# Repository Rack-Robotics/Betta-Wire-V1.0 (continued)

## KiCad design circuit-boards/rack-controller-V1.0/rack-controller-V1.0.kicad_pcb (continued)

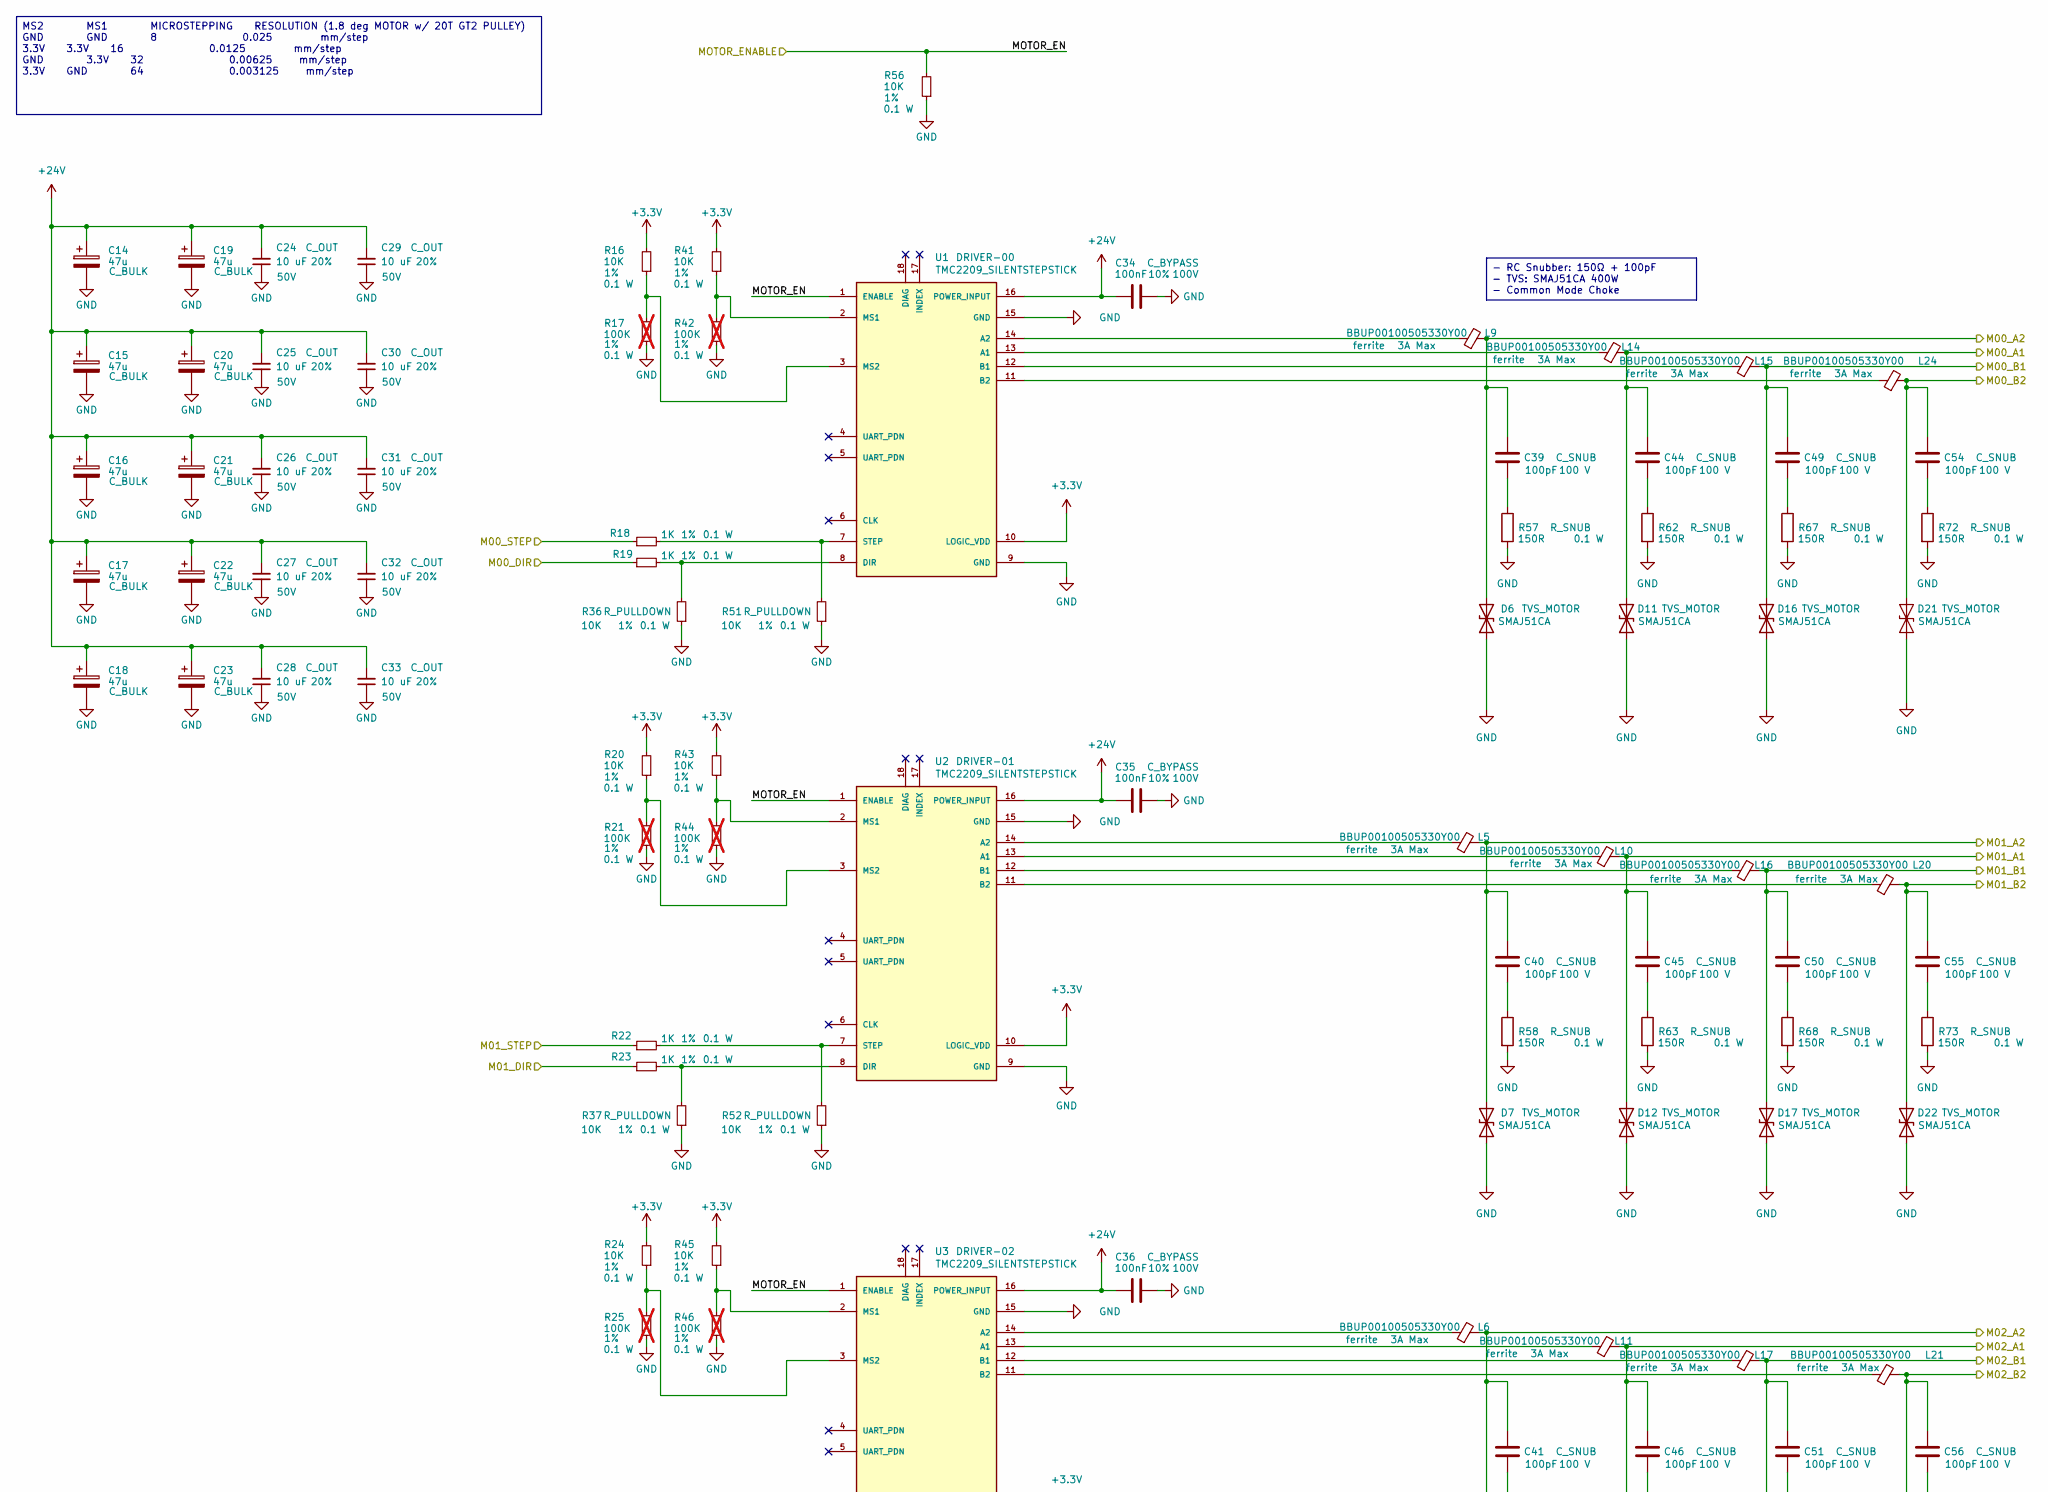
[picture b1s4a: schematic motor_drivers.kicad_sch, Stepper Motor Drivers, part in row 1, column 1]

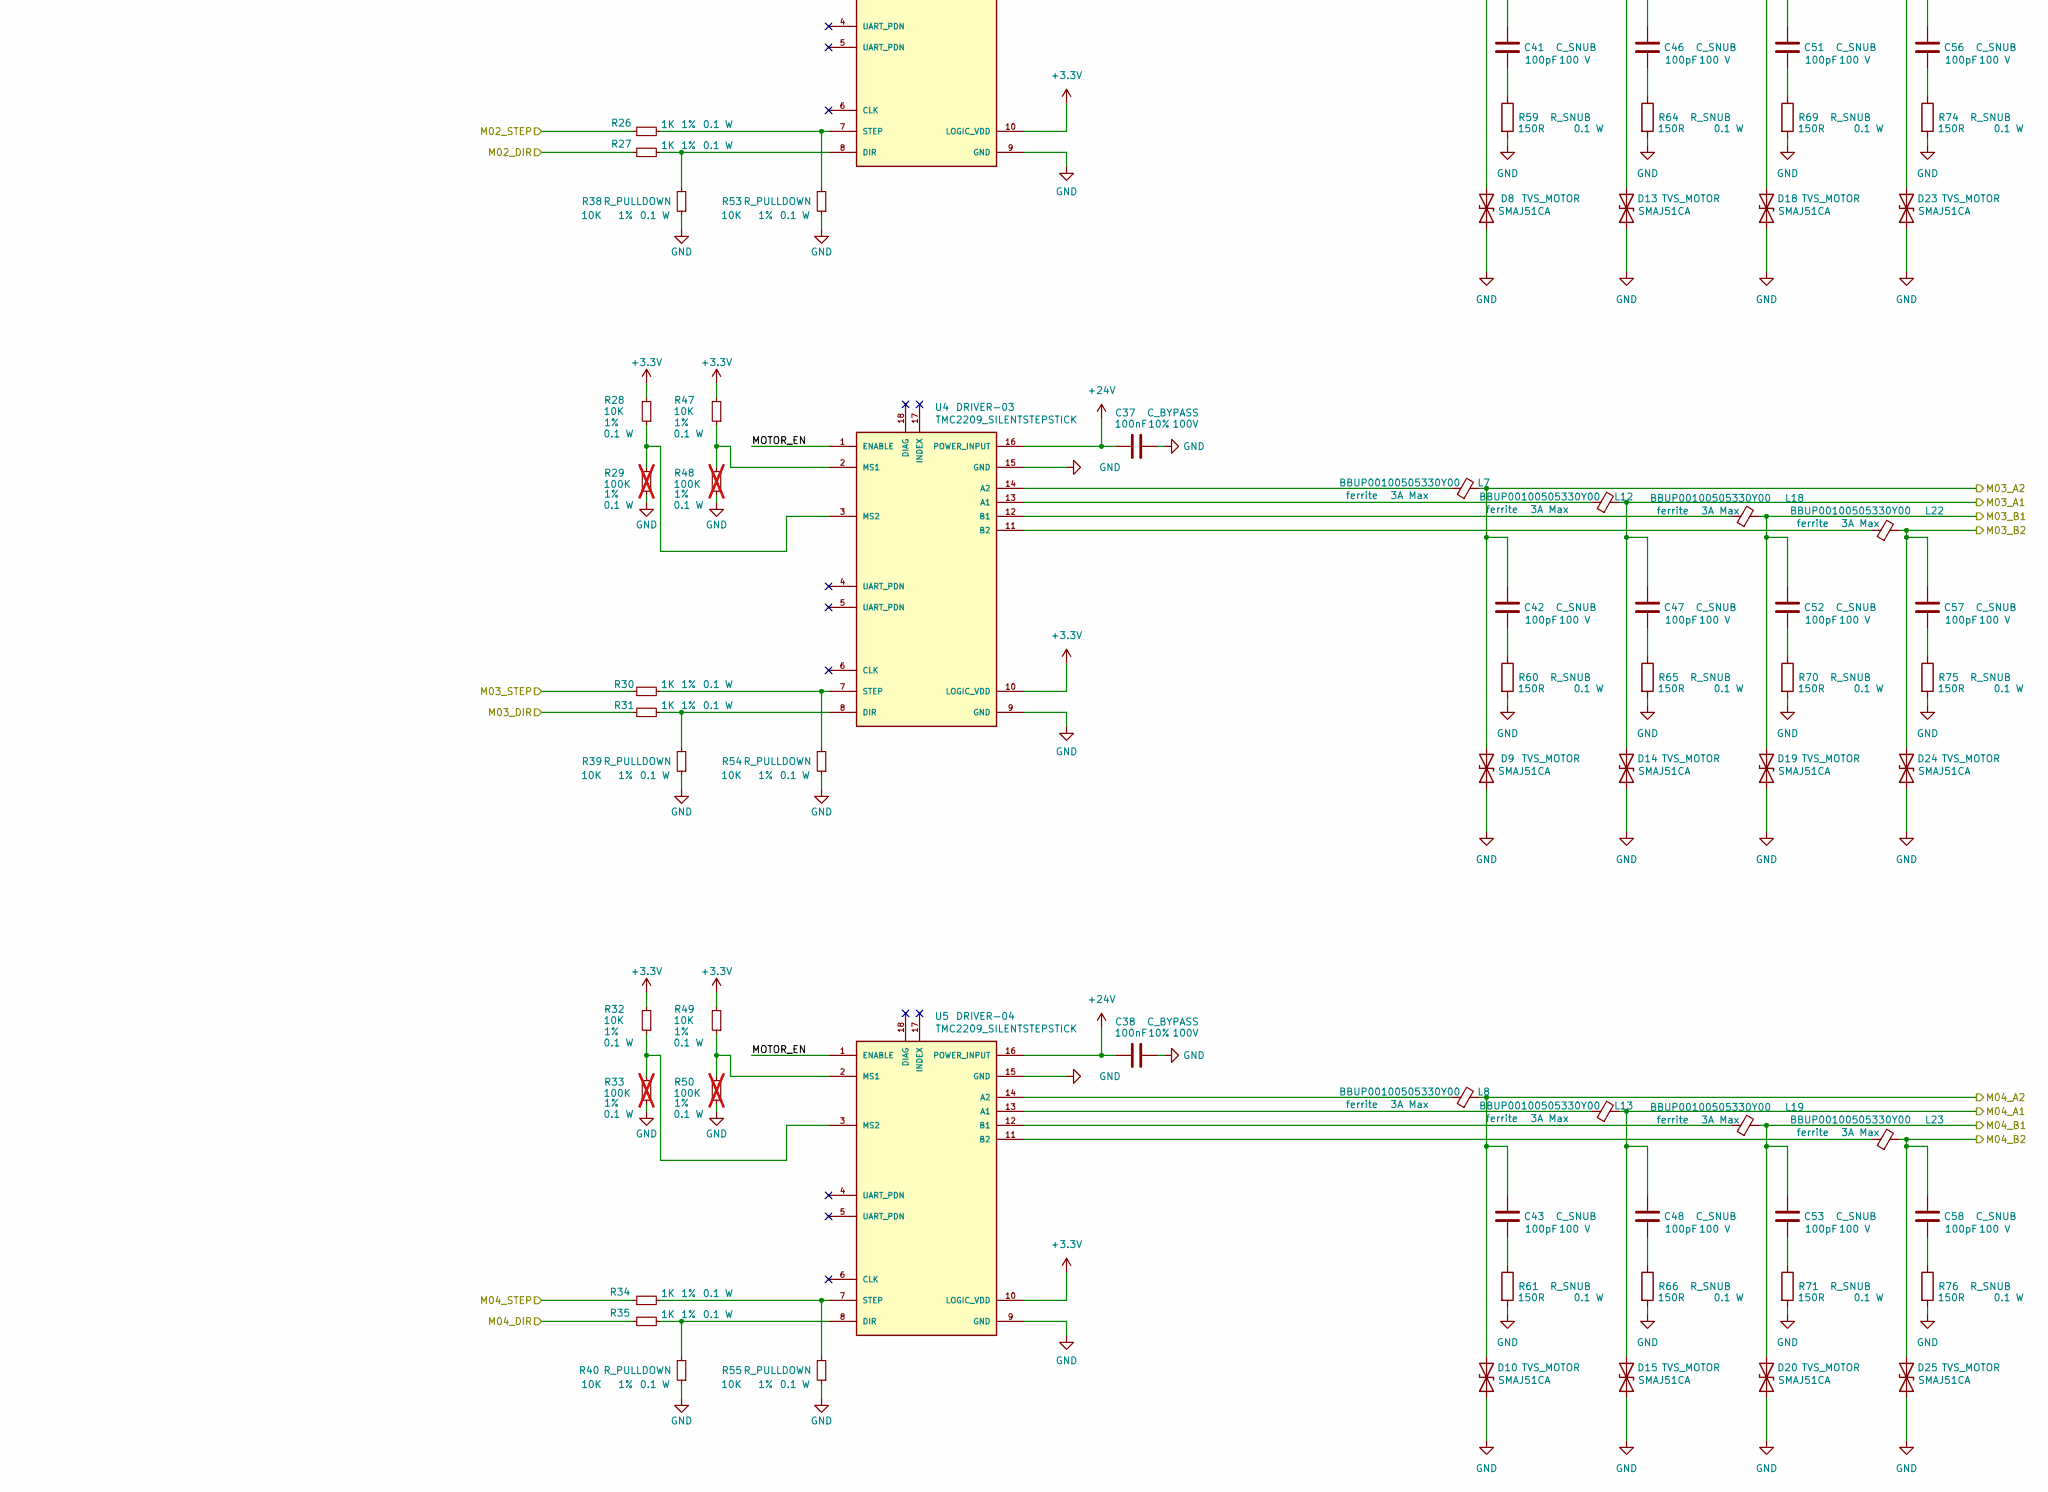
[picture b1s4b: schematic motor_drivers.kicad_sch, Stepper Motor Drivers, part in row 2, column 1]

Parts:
C14, C15, C16, C17, C18, C19, C20, C21, C22, C23: 47u; CP_Elec_6.3x5.9; Manufacturer# 35SVPK47M; LCSC Part # C264034
C24, C25, C26, C27, C28, C29, C30, C31, C32, C33: 10 uF; C_1206_3216Metric; Tolerance 20%; Max Voltage 50V; Manufacturer# CL31A106MBHNNNE; LCSC Part # C96600
C34, C35, C36, C37, C38: 100nF; C_0603_1608Metric; Voltage 100V; Tolerance 10%; Manufacturer# CC0603KRX7R0BB104; LCSC Part # C113803
C39, C40, C41, C42, C43, C44, C45, C46, C47, C48, C49, C50, C51, C52, C53, C54, C55, C56, C57, C58: 100pF; C_0402_1005Metric; Voltage 100 V; Manufacturer# CC0402JRNPO0BN101; LCSC Part # C576700
D6, D7, D8, D9, D10, D11, D12, D13, D14, D15, D16, D17, D18, D19, D20, D21, D22, D23, D24, D25: SMAJ51CA; D_SMA; Manufacturer# SMAJ60CA-13-F; LCSC Part # C135003
L5, L6, L7, L8, L9, L10, L11, L12, L13, L14, L15, L16, L17, L18, L19, L20, L21, L22, L23, L24: BBUP00100505330Y00; L_0402_1005Metric; Manufacturer# BLM15AX100SN1D; LCSC Part # C668299
R16, R20, R24, R28, R32, R36, R37, R38, R39, R40, R41, R43, R45, R47, R49, R51, R52, R53, R54, R55, R56: 10K; R_0603_1608Metric; Tolerance 1%; Manufacturer# RC0603BR-0710KL; LCSC Part # C98220
R17, R21, R25, R29, R33, R42, R44, R46, R48, R50: 100K; R_0603_1608Metric; Tolerance 1%; Manufacturer# RT0603FRE07100KL; LCSC Part # C728638; not fitted
R18, R19, R22, R23, R26, R27, R30, R31, R34, R35: 1K; R_0603_1608Metric; Tolerance 1%; Manufacturer# RC0603FR-071KL; LCSC Part # C22548
R57, R58, R59, R60, R61, R62, R63, R64, R65, R66, R67, R68, R69, R70, R71, R72, R73, R74, R75, R76: 150R; R_0603_1608Metric; Tolerance 1%; Manufacturer# RC0603FR-07150RL; LCSC Part # C114608
U1, U2, U3, U4, U5: TMC2209_SILENTSTEPSTICK; BTT_TMC2209_V1.3; Manufacturer# TMC2209_V1.3; LCSC Part # NULL

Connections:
+3.3V: R16.2, R20.2, R24.2, R28.2, R32.2, R41.2, R43.2, R45.2, R47.2, R49.2, U1.10 (LOGIC_VDD), U2.10 (LOGIC_VDD), U3.10 (LOGIC_VDD), U4.10 (LOGIC_VDD), U5.10 (LOGIC_VDD); also elsewhere on the board
+24V: C14.1, C15.1, C16.1, C17.1, C18.1, C19.1, C20.1, C21.1, C22.1, C23.1, C24.2, C25.2, C26.2, C27.2, C28.2, C29.2, C30.2, C31.2, C32.2, C33.2, C34.2, C35.2, C36.2, C37.2, C38.2, U1.16 (POWER_INPUT), U2.16 (POWER_INPUT), U3.16 (POWER_INPUT), U4.16 (POWER_INPUT), U5.16 (POWER_INPUT); also elsewhere on the board
/GPIO_05: R18.1; also elsewhere on the board
/GPIO_06: R56.2, U1.1 (ENABLE), U2.1 (ENABLE), U3.1 (ENABLE), U4.1 (ENABLE), U5.1 (ENABLE); also elsewhere on the board
/GPIO_14 (UART_TX): R35.1; also elsewhere on the board
/GPIO_15 (UART_RX): R34.1; also elsewhere on the board
/GPIO_17: R30.1; also elsewhere on the board
/GPIO_18 (PCM_CLK): R31.1; also elsewhere on the board
/GPIO_22: R23.1; also elsewhere on the board
/GPIO_23: R26.1; also elsewhere on the board
/GPIO_24: R22.1; also elsewhere on the board
/GPIO_25: R19.1; also elsewhere on the board
/GPIO_27: R27.1; also elsewhere on the board
/stepper_motor_drivers/M00_A1: C44.1, D11.2 (A2), L14.2; also elsewhere on the board
/stepper_motor_drivers/M00_A2: C39.1, D6.2 (A2), L9.2; also elsewhere on the board
/stepper_motor_drivers/M00_B1: C49.1, D16.2 (A2), L15.2; also elsewhere on the board
/stepper_motor_drivers/M00_B2: C54.1, D21.2 (A2), L24.2; also elsewhere on the board
/stepper_motor_drivers/M01_A1: C45.1, D12.2 (A2), L10.2; also elsewhere on the board
/stepper_motor_drivers/M01_A2: C40.1, D7.2 (A2), L5.2; also elsewhere on the board
/stepper_motor_drivers/M01_B1: C50.1, D17.2 (A2), L16.2; also elsewhere on the board
/stepper_motor_drivers/M01_B2: C55.1, D22.2 (A2), L20.2; also elsewhere on the board
/stepper_motor_drivers/M02_A1: C46.1, D13.2 (A2), L11.2; also elsewhere on the board
/stepper_motor_drivers/M02_A2: C41.1, D8.2 (A2), L6.2; also elsewhere on the board
/stepper_motor_drivers/M02_B1: C51.1, D18.2 (A2), L17.2; also elsewhere on the board
/stepper_motor_drivers/M02_B2: C56.1, D23.2 (A2), L21.2; also elsewhere on the board
/stepper_motor_drivers/M03_A1: C47.1, D14.2 (A2), L12.2; also elsewhere on the board
/stepper_motor_drivers/M03_A2: C42.1, D9.2 (A2), L7.2; also elsewhere on the board
/stepper_motor_drivers/M03_B1: C52.1, D19.2 (A2), L18.2; also elsewhere on the board
/stepper_motor_drivers/M03_B2: C57.1, D24.2 (A2), L22.2; also elsewhere on the board
/stepper_motor_drivers/M04_A1: C48.1, D15.2 (A2), L13.2; also elsewhere on the board
/stepper_motor_drivers/M04_A2: C43.1, D10.2 (A2), L8.2; also elsewhere on the board
/stepper_motor_drivers/M04_B1: C53.1, D20.2 (A2), L19.2; also elsewhere on the board
/stepper_motor_drivers/M04_B2: C58.1, D25.2 (A2), L23.2; also elsewhere on the board
GND: C14.2, C15.2, C16.2, C17.2, C18.2, C19.2, C20.2, C21.2, C22.2, C23.2, C24.1, C25.1, C26.1, C27.1, C28.1, C29.1, C30.1, C31.1, C32.1, C33.1, C34.1, C35.1, C36.1, C37.1, C38.1, D6.1 (A1), D7.1 (A1), D8.1 (A1), D9.1 (A1), D10.1 (A1), D11.1 (A1), D12.1 (A1), D13.1 (A1), D14.1 (A1), D15.1 (A1), D16.1 (A1), D17.1 (A1), D18.1 (A1), D19.1 (A1), D20.1 (A1), D21.1 (A1), D22.1 (A1), D23.1 (A1), D24.1 (A1), D25.1 (A1), R17.1, R21.1, R25.1, R29.1, R33.1, R36.1, R37.1, R38.1, R39.1, R40.1, R42.1, R44.1, R46.1, R48.1, R50.1, R51.1, R52.1, R53.1, R54.1, R55.1, R56.1, R57.2, R58.2, R59.2, R60.2, R61.2, R62.2, R63.2, R64.2, R65.2, R66.2, R67.2, R68.2, R69.2, R70.2, R71.2, R72.2, R73.2, R74.2, R75.2, R76.2, U1.9 (GND), U1.15 (GND), U2.9 (GND), U2.15 (GND), U3.9 (GND), U3.15 (GND), U4.9 (GND), U4.15 (GND), U5.9 (GND), U5.15 (GND); also elsewhere on the board
unnamed: C39.2, R57.1
unnamed: C40.2, R58.1
unnamed: C41.2, R59.1
unnamed: C42.2, R60.1
unnamed: C43.2, R61.1
unnamed: C44.2, R62.1
unnamed: C45.2, R63.1
unnamed: C46.2, R64.1
unnamed: C47.2, R65.1
unnamed: C48.2, R66.1
unnamed: C49.2, R67.1
unnamed: C50.2, R68.1
unnamed: C51.2, R69.1
unnamed: C52.2, R70.1
unnamed: C53.2, R71.1
unnamed: C54.2, R72.1
unnamed: C55.2, R73.1
unnamed: C56.2, R74.1
unnamed: C57.2, R75.1
unnamed: C58.2, R76.1
unnamed: L14.1, U1.13 (A1)
unnamed: L9.1, U1.14 (A2)
unnamed: L15.1, U1.12 (B1)
unnamed: L24.1, U1.11 (B2)
unnamed: R19.2, R36.2, U1.8 (DIR)
unnamed: R41.1, R42.2, U1.2 (MS1)
unnamed: R16.1, R17.2, U1.3 (MS2)
unnamed: R18.2, R51.2, U1.7 (STEP)
unnamed: L10.1, U2.13 (A1)
unnamed: L5.1, U2.14 (A2)
unnamed: L16.1, U2.12 (B1)
unnamed: L20.1, U2.11 (B2)
unnamed: R23.2, R37.2, U2.8 (DIR)
unnamed: R43.1, R44.2, U2.2 (MS1)
unnamed: R20.1, R21.2, U2.3 (MS2)
unnamed: R22.2, R52.2, U2.7 (STEP)
unnamed: L11.1, U3.13 (A1)
unnamed: L6.1, U3.14 (A2)
unnamed: L17.1, U3.12 (B1)
unnamed: L21.1, U3.11 (B2)
unnamed: R27.2, R38.2, U3.8 (DIR)
unnamed: R45.1, R46.2, U3.2 (MS1)
unnamed: R24.1, R25.2, U3.3 (MS2)
unnamed: R26.2, R53.2, U3.7 (STEP)
unnamed: L12.1, U4.13 (A1)
unnamed: L7.1, U4.14 (A2)
unnamed: L18.1, U4.12 (B1)
unnamed: L22.1, U4.11 (B2)
unnamed: R31.2, R39.2, U4.8 (DIR)
unnamed: R47.1, R48.2, U4.2 (MS1)
unnamed: R28.1, R29.2, U4.3 (MS2)
unnamed: R30.2, R54.2, U4.7 (STEP)
unnamed: L13.1, U5.13 (A1)
unnamed: L8.1, U5.14 (A2)
unnamed: L19.1, U5.12 (B1)
unnamed: L23.1, U5.11 (B2)
unnamed: R35.2, R40.2, U5.8 (DIR)
unnamed: R49.1, R50.2, U5.2 (MS1)
unnamed: R32.1, R33.2, U5.3 (MS2)
unnamed: R34.2, R55.2, U5.7 (STEP)

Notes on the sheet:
- RC Snubber: 150Ω + 100pF - TVS: SMAJ51CA 400W - Common Mode Choke
MS2 MS1 MICROSTEPPING RESOLUTION (1.8 deg MOTOR w/ 20T GT2 PULLEY) GND GND 8 0.025 mm/step 3.3V 3.3V 16 0.0125 mm/step GND 3.3V 32 0.00625 mm/step 3.3V GND 64 0.003125 mm/step

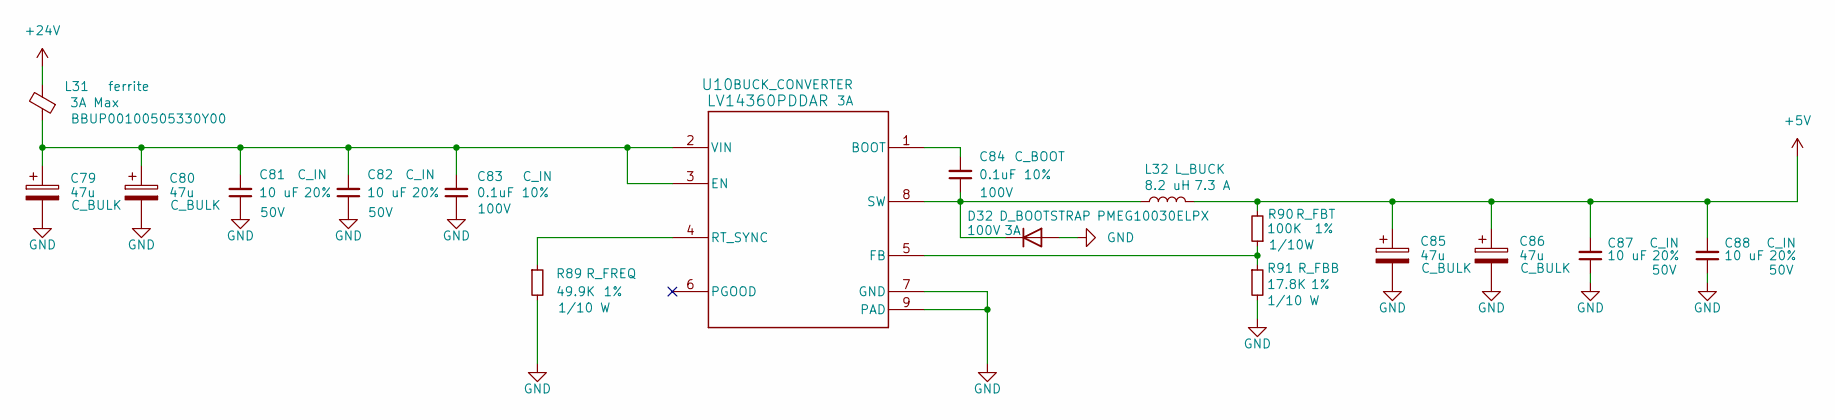
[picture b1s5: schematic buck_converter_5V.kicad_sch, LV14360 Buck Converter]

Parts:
C79, C80, C85, C86: 47u; CP_Elec_6.3x5.9; Manufacturer# 35SVPK47M; LCSC Part # C264034
C81, C82, C87, C88: 10 uF; C_1206_3216Metric; Tolerance 20%; Max Voltage 50V; Manufacturer# CL31A106MBHNNNE; LCSC Part # C96600
C83, C84: 0.1uF; C_0603_1608Metric; Tolerance 10%; Max Voltage 100V; Manufacturer# CC0603KRX7R0BB104; LCSC Part # C113803
D32: PMEG10030ELPX; D_SOD-128; Max Voltage 100V; Manufacturer# PMEG10030ELPX; LCSC Part # C5260346
L31: BBUP00100505330Y00; L_0402_1005Metric; Manufacturer# BLM15AX100SN1D; LCSC Part # C668299
L32: 8.2 uH; SRR1210-8R2Y; Manufacturer# SRR1210-8R2Y
R89: 49.9K; R_0603_1608Metric; Tolerance 1%; Manufacturer# RC0603FR-0749K9L
R90: 100K; R_0603_1608Metric; Tolerance 1%; Manufacturer# RT0603FRE07100KL; LCSC Part # C728638
R91: 17.8K; R_0603_1608Metric; Tolerance 1%; Manufacturer# RC0603FR-0717K8L; LCSC Part # C185364
U10: LV14360PDDAR; Manufacturer# LV14360PDDAR; LCSC Part # C2864599

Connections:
+5V: C85.1, C86.1, C87.2, C88.2, L32.2, R90.2; also elsewhere on the board
+24V: L31.2; also elsewhere on the board
GND: C79.2, C80.2, C81.1, C82.1, C83.1, C85.2, C86.2, C87.1, C88.1, D32.2 (A), R89.2, R91.2, U10.7 (GND), U10.9 (PAD); also elsewhere on the board
unnamed: C84.1, D32.1 (K), L32.1, U10.8 (SW)
unnamed: C84.2, U10.1 (BOOT)
unnamed: C79.1, C80.1, C81.2, C82.2, C83.2, L31.1, U10.2 (VIN), U10.3 (EN)
unnamed: R90.1, R91.1, U10.5 (FB)
unnamed: R89.1, U10.4 (RT_SYNC)

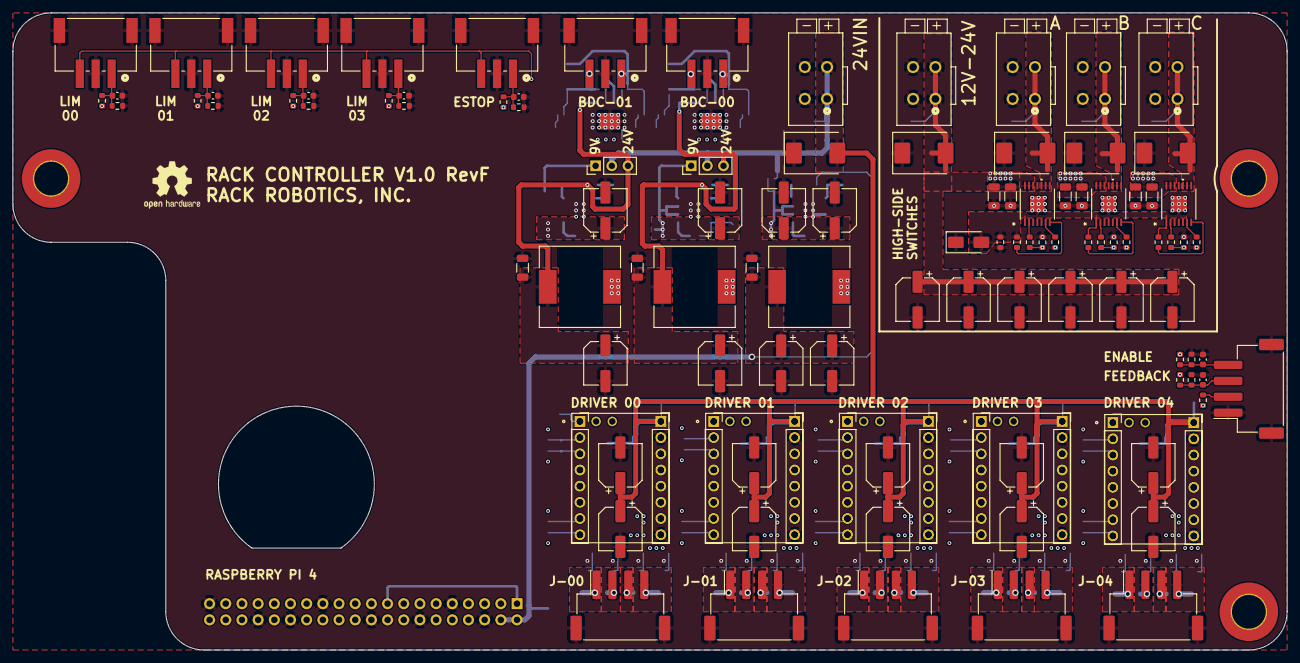
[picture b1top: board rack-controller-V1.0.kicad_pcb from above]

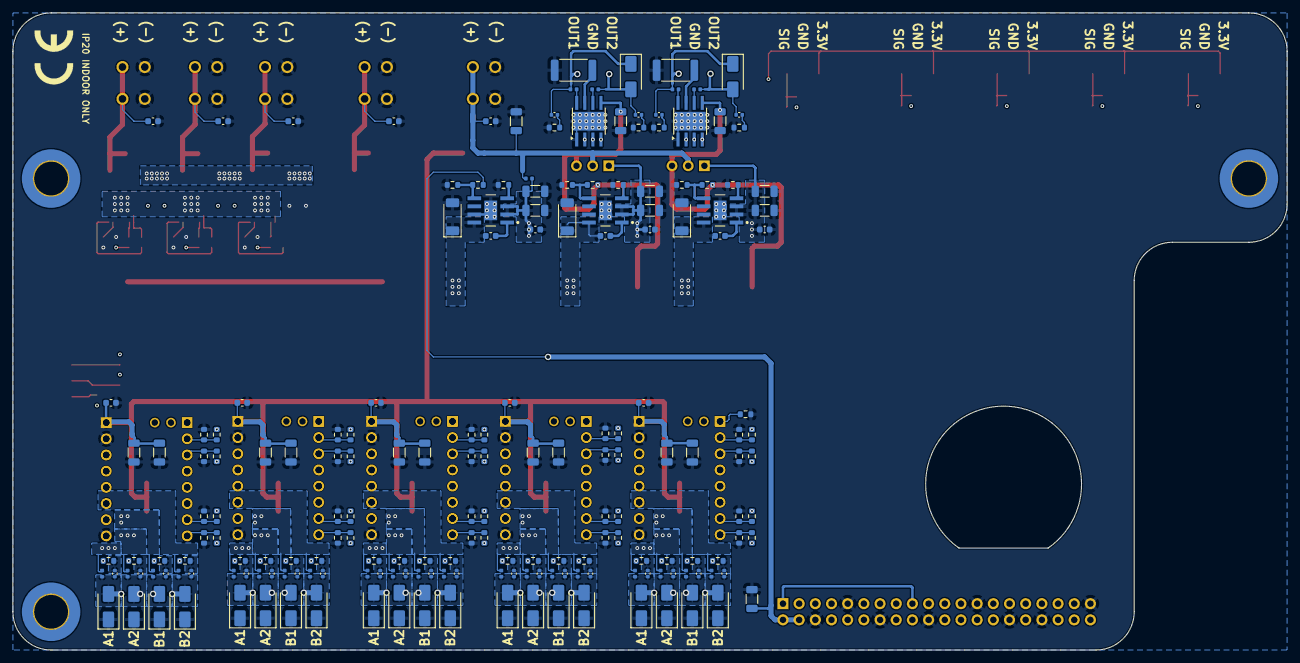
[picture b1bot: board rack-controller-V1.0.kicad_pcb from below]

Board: 6 copper layers, 200.0 x 100.0 mm, 311 parts (191 on the bottom side), 163 nets.

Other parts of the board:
HDR1, HDR1#2, HDR2, HDR2#2, HDR3, HDR4, HDR5, HDR6, HDR7, HDR8: PinSocket_1x08_P2.54mm_Vertical
RP4: Raspberry_Pi; raspberrypi-outline

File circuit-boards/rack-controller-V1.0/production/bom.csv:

Designator,Footprint,Quantity,Value,LCSC Part #
"C10, C65, C66, C67, C68, C8, C83, C84",0603,8,0.1uF,C113803
"C100, C14, C15, C16, C17, C18, C19, C20, C21, C22, C23, C60, C62, C69, C70, C79, C80, C85, C86, C95, C96, C97, C98, C99",CP_Elec_6.3x5.9,24,47u,C264034
"C11, C12, C13, C34, C35, C36, C37, C38",0603,8,100nF,C113803
"C24, C25, C26, C27, C28, C29, C30, C31, C32, C33, C59, C61, C63, C64, C71, C72, C73, C74, C81, C82, C87, C88, C89, C9, C90, C91, C92, C93, C94",1206,29,10 uF,C96600
"C3, C4, C5, C6",0603,4,2.2uF,C106853
"C39, C40, C41, C42, C43, C44, C45, C46, C47, C48, C49, C50, C51, C52, C53, C54, C55, C56, C57, C58, C75, C76, C77, C78",0402,24,100pF,C576700
"D1, D2, D3, D4, D5",D_SMC,5,SMCJ60A,C2943780
"D10, D11, D12, D13, D14, D15, D16, D17, D18, D19, D20, D21, D22, D23, D24, D25, D30, D31, D6, D7, D8, D9",D_SMA,22,SMAJ51CA,C135003
"D26, D27, D32",D_SOD-128,3,PMEG10030ELPX,C5260346
D33,D_SMA,1,US1M-13-F,C99333
"HDR1_2, HDR1, HDR2_2, HDR2, HDR3, HDR4, HDR5, HDR6, HDR7, HDR8",PinSocket_1x08_P2.54mm_Vertical,10,PinSocket_1x08_P2.54mm_Vertical,C27438
"J1, J17, J18, J19, J9",2601-1102,5,2601-1102,
"J10, J11, J12, J13, J14, J6",JST_XH_S4B-XH-SM4-TB_1x04-1MP_P2.50mm_Horizontal_custom,6,S4B-XH-SM4-TB,C161861
"J15, J16, J2, J3, J4, J5, J7",S3B-XH-SM4-TB,7,S3B-XH-SM4-TB,C161860
J20,PinHeader_1x03_P2.54mm_Vertical,1,BDC_00_SELECTOR,C5360899
J21,PinHeader_1x03_P2.54mm_Vertical,1,BDC_01_SELECTOR,C5360899
J8,raspberrypi,1,Raspberry Pi GPIO Header,NULL
"L10, L11, L12, L13, L14, L15, L16, L17, L18, L19, L20, L21, L22, L23, L24, L27, L28, L29, L30, L31, L5, L6, L7, L8, L9",0402,25,BBUP00100505330Y00,C668299
"L25, L26, L32",SRR1210-8R2Y,3,8.2 uH,
"R1, R100, R104, R18, R19, R2, R22, R23, R26, R27, R30, R31, R34, R35, R5, R6, R7, R8, R9, R96, R98",0603,21,1K,C22548
"R10, R11, R12, R13, R14, R16, R20, R24, R28, R3, R32, R36, R37, R38, R39, R4, R40, R41, R43, R45, R47, R49, R51, R52, R53, R54, R55, R56, R92, R93, R94",0603,31,10K,C98220
"R101, R102, R103",0603,3,19.6K,C245925
"R57, R58, R59, R60, R61, R62, R63, R64, R65, R66, R67, R68, R69, R70, R71, R72, R73, R74, R75, R76, R85, R86, R87, R88",0603,24,150R,C114608
"R77, R78, R89",0603,3,49.9K,
"R79, R81, R90",0603,3,100K,C728638
"R80, R82",0603,2,9.09K,C185301
"R83, R84",2512,2,0.11R,C46595965
R91,0603,1,17.8K,C185364
"R95, R97, R99",0603,3,2.2K,C114662
RP4,raspberrypi-outline,1,Raspberry_Pi,
"U1, U2, U3, U4, U5",BTT_TMC2209_V1.3,5,TMC2209_SILENTSTEPSTICK,NULL
"U10, U6, U7",LV14360PDDAR,3,LV14360PDDAR,C2864599
"U11, U12, U13",TPS1HTC30-Q1,3,TPS1HTC30AQPWPRQ1,C22414694
"U8, U9",DRV8870DDA,2,DRV8870DDA,C86590

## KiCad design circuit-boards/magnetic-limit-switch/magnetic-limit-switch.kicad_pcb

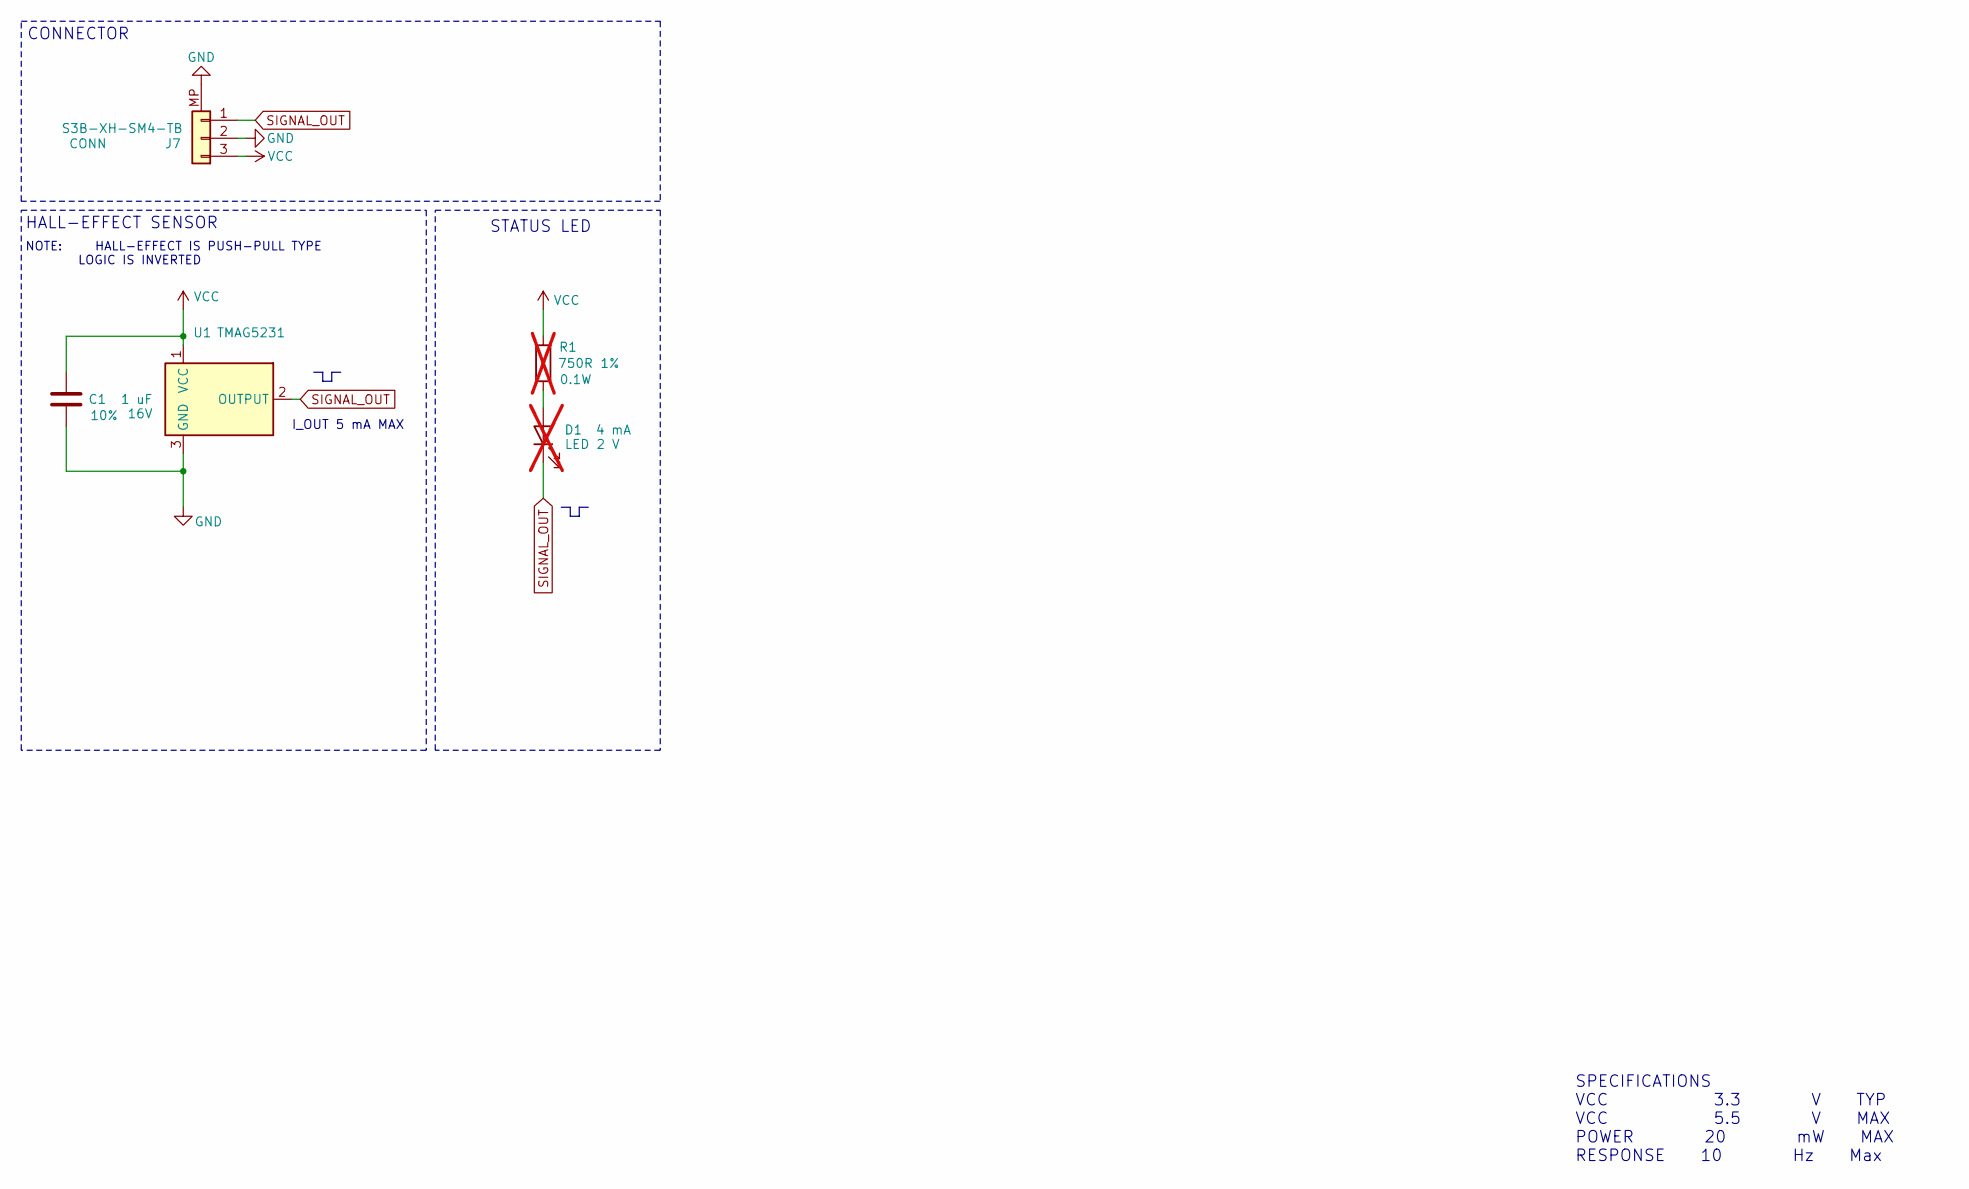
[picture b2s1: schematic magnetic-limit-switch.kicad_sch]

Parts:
C1: 1 uF; C_0603_1608Metric; Tolerance 10%; Manufacterer# CC0603KRX7R7BB105; LCSC Part # C106248
D1: LED; LED_0603_1608Metric; Manufacterer# LTST-C193KFKT-5A; LCSC Part # C284922; not fitted
J7: S3B-XH-SM4-TB; JST_XH_S3B-XH-SM4-TB_1x03-1MP_P2.50mm_Horizontal; Manufacterer# S3B-XH-SM4-TB; LCSC Part # C161860
R1: 750R; R_0603_1608Metric; Tolerance 1%; Manufacterer# RC0603FR-07750RL; LCSC Part # C114635; not fitted
U1: TMAG5231; SOT-23-3; Manufacterer# TMAG5231A2DQDBZR; LCSC Part # C17378950

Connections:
GND: C1.1, J7.2, J7.MP, U1.3 (GND)
unnamed: D1.2 (A), R1.1
SIGNAL_OUT: D1.1 (K), J7.1, U1.2 (OUTPUT)
VCC: C1.2, J7.3, R1.2, U1.1 (VCC)

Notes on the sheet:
NOTE: HALL-EFFECT IS PUSH-PULL TYPE LOGIC IS INVERTED
CONNECTOR
HALL-EFFECT SENSOR
STATUS LED
SPECIFICATIONS VCC 3.3 V TYP VCC 5.5 V MAX POWER 20 mW MAX RESPONSE 10 Hz Max
I_OUT 5 mA MAX

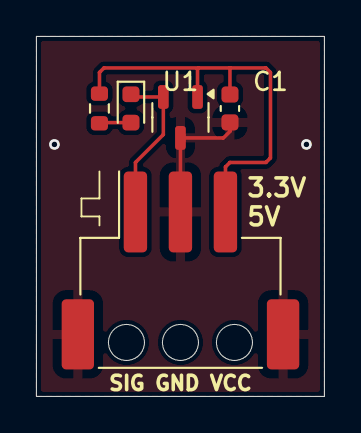
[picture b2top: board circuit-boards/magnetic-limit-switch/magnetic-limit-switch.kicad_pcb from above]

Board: 2 copper layers, 16.0 x 20.0 mm, 5 parts (0 on the bottom side), 4 nets.

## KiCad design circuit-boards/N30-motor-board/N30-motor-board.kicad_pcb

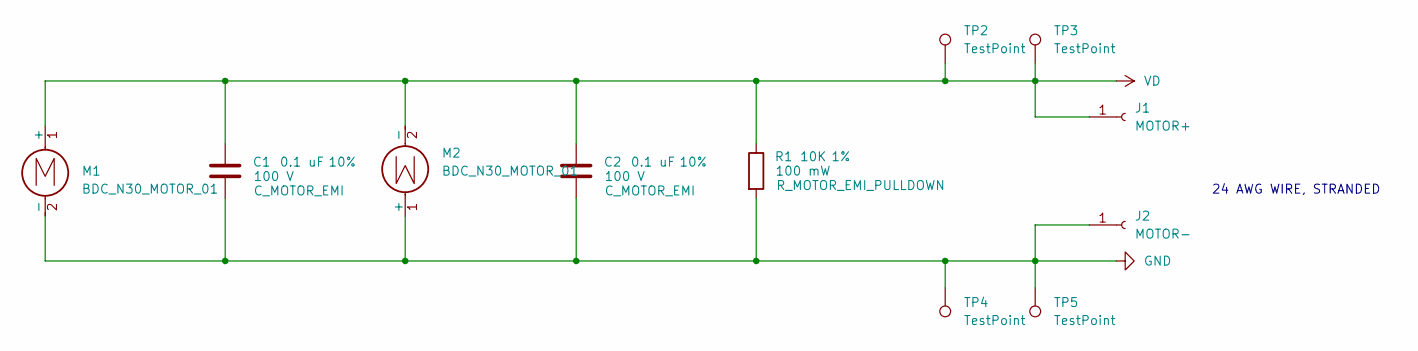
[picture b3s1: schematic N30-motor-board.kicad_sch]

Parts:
C1, C2: 0.1 uF; C_0603_1608Metric; Max Voltage 100 V; Tolerance 10%; Manufacturer# CC0603KRX7R0BB104; LCSC Part # C113803
J1: MOTOR+; SolderWire-0.25sqmm_1x01_D0.65mm_OD1.7mm
J2: MOTOR-; SolderWire-0.25sqmm_1x01_D0.65mm_OD1.7mm
M1, M2: BDC_N30_MOTOR_01; N30_MOTOR_TH
R1: 10K; R_0603_1608Metric; Tolerance 1%; Manufacturer# RC0603FR-0710KL; LCSC Part # C98220
TP2, TP3, TP4, TP5: TestPoint; TestPoint_Pad_2.0x2.0mm

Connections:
GND: C1.2, C2.2, J2.1, M1.2 (-), M2.1 (+), R1.2, TP4.1, TP5.1
VD: C1.1, C2.1, J1.1, M1.1 (+), M2.2 (-), R1.1, TP2.1, TP3.1

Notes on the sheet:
24 AWG WIRE, STRANDED

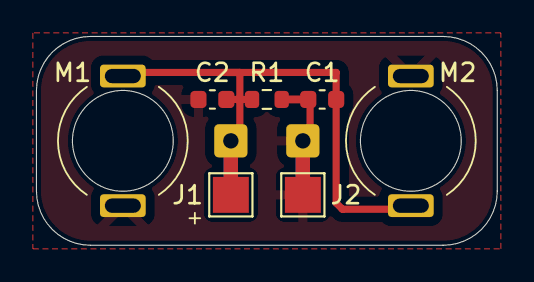
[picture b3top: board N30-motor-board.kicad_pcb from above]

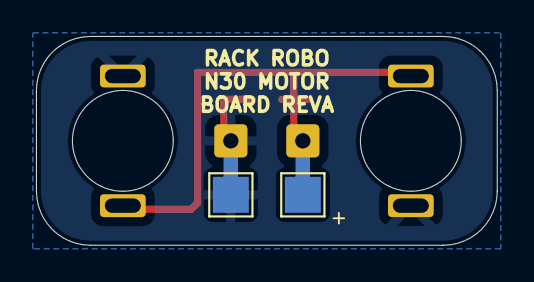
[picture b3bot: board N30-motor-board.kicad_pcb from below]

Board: 2 copper layers, 25.6 x 11.6 mm, 11 parts (2 on the bottom side), 2 nets.
